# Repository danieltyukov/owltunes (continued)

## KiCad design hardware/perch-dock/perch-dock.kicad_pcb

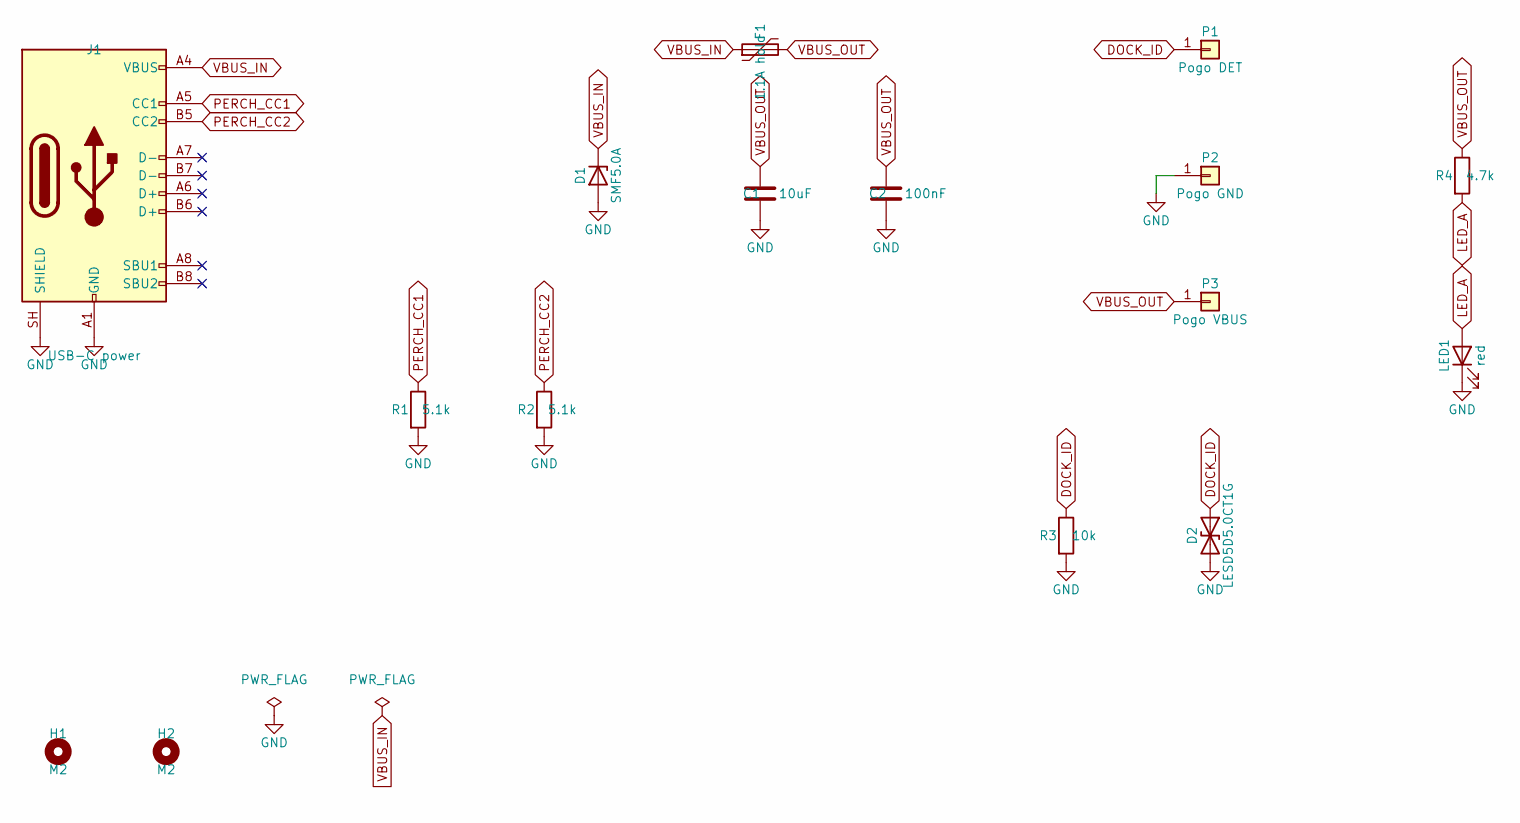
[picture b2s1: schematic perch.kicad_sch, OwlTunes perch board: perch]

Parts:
C1: 10uF; C_0603_1608Metric; MPN CL10A106KP8NNNC; LCSC Part # C19702
C2: 100nF; C_0402_1005Metric; MPN CL05B104KO5NNNC; LCSC Part # C1525
D1: SMF5.0A; D_SOD-123F; MPN SMF5.0A; LCSC Part # C193402
D2: LESD5D5.0CT1G; D_SOD-523; MPN LESD5D5.0CT1G; LCSC Part # C5274290
F1: 1.1A hold; Fuse_1206_3216Metric; MPN nSMD110; LCSC Part # C71465
H1, H2: M2; MountingHole_2.2mm_M2
J1: USB-C power; USB_C_Receptacle_HRO_TYPE-C-31-M-12; MPN TYPE-C-31-M-12; LCSC Part # C165948
LED1: red; LED_0603_1608Metric; MPN KT-0603R; LCSC Part # C2286
P1: Pogo DET; PogoPin_Xinyangze_YZ71215080P-02; MPN YZ71215080P-02; LCSC Part # C5157364
P2: Pogo GND; PogoPin_Xinyangze_YZ71215080P-02; MPN YZ71215080P-02; LCSC Part # C5157364
P3: Pogo VBUS; PogoPin_Xinyangze_YZ71215080P-02; MPN YZ71215080P-02; LCSC Part # C5157364
R1, R2: 5.1k; R_0402_1005Metric; MPN 0402WGF5101TCE; LCSC Part # C25905
R3: 10k; R_0402_1005Metric; MPN 0402WGF1002TCE; LCSC Part # C25744
R4: 4.7k; R_0402_1005Metric; MPN 0402WGF4701TCE; LCSC Part # C25900

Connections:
DOCK_ID: D2.1 (A1), P1.1, R3.1
GND: C1.2, C2.2, D1.2 (A), D2.2 (A2), J1.A1 (GND), J1.A12 (GND), J1.B1 (GND), J1.B12 (GND), J1.SH (SHIELD), LED1.1 (K), P2.1, R1.2, R2.2, R3.2
LED_A: LED1.2 (A), R4.2
PERCH_CC1: J1.A5 (CC1), R1.1
PERCH_CC2: J1.B5 (CC2), R2.1
VBUS_IN: D1.1 (K), F1.1, J1.A4 (VBUS), J1.A9 (VBUS), J1.B4 (VBUS), J1.B9 (VBUS)
VBUS_OUT: C1.1, C2.1, F1.2, P3.1, R4.1

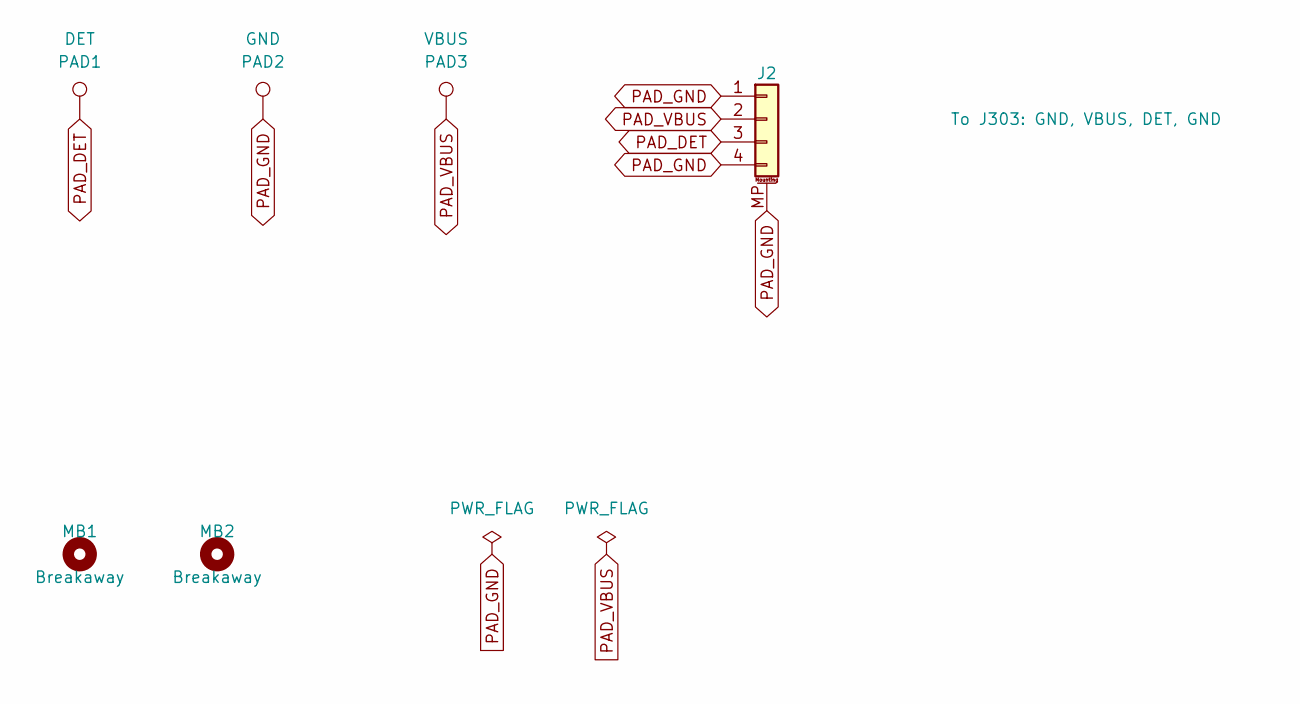
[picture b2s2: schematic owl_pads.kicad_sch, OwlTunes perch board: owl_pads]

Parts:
J2: To J303: GND, VBUS, DET, GND; JST_SH_SM04B-SRSS-TB_1x04-1MP_P1.00mm_Horizontal; MPN SM04B-SRSS-TB(LF)(SN); LCSC Part # C160404
MB1, MB2: Breakaway; MouseBite_2.5mm_2x0.6mm
PAD1: DET; TestPoint_Pad_D3.0mm
PAD2: GND; TestPoint_Pad_D3.0mm
PAD3: VBUS; TestPoint_Pad_D3.0mm

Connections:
PAD_DET: J2.3, PAD1.1
PAD_GND: J2.1, J2.4, J2.MP (MountPin), PAD2.1
PAD_VBUS: J2.2, PAD3.1

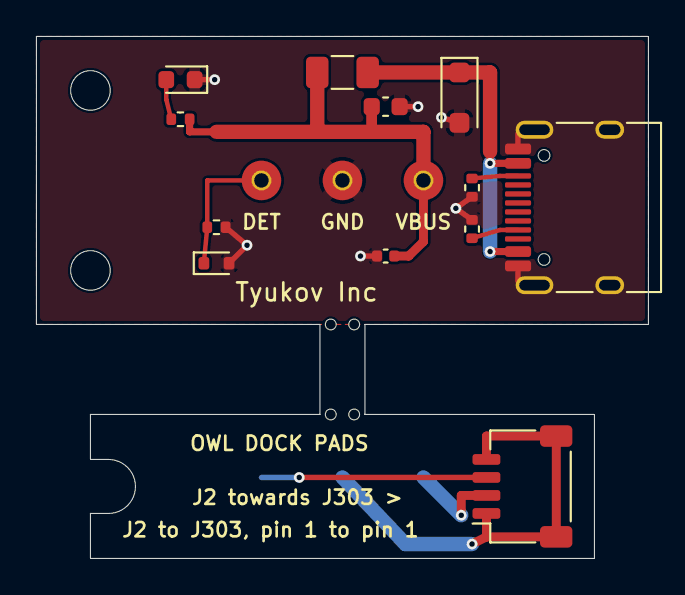
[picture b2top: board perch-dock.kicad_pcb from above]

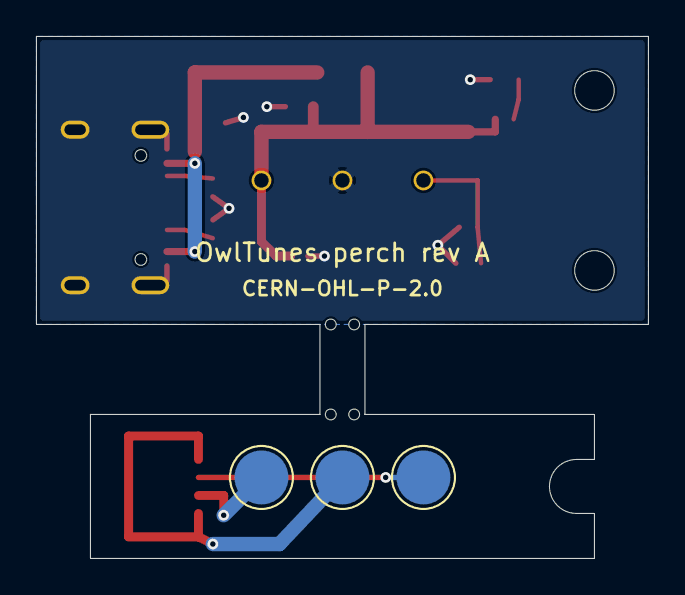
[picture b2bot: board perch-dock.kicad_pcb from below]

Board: 2 copper layers, 34.0 x 29.0 mm, 22 parts (3 on the bottom side), 10 nets.

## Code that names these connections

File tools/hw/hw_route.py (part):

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        ("GND", "via", [(13.85, -3.45), (13.85, -2.55), (12.3, -3.05), (12.3, -3.65), (16.3, -6.7), (16.35, -4.75),
                        (17.2, -0.2), (17.2, 1.4), (13.28, -0.7), (9.8, -1.2)]),
    ],
    # Charger (BQ24073): VIN_CHG from pin 13 to C101, on to the D101 and D102 cathodes; VSYS from
    # pins 10 and 11 to C102 and TP102 (on to the TPS63802 in part C, with a layer change at each
    # end: In2 stays GND under U101, U103 and their caps, so a VSYS pour only runs between them);
    # VBAT from pins 2 and 3 to C103, then up between C103 and R103, clear of the H1 boss ring, to
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    # VIN_CHG taps from the D101/D102 cathode run: east to TP101 above the diode anodes (D101's
    # VBUS_USB anode stays open to the east and south of TP101); and to R103, the CHG_EN2 pull-up,
    # which sits between the VBAT and VSYS runs north of U101, so that tap crosses on F.Cu west of
    # U101 and leaves the ground below U101 pin 1 free for BAT_NTC. Its top via sits at y 1.8, low
    # enough for the +3V3 link (late_links) to pass between it and the VSYS F.Cu run at y 3.25.
    "vin_chg_taps": [
        ("VIN_CHG", 0.5, [(24.1, -4.0), (24.3, -4.2), (29.3, -4.2), (29.3, -5.5)]),
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        ("VIN_CHG", 0.25, [(22.5, 1.8), (22.5, 2.99)]),
        ("VIN_CHG", "via", [(23.4, -4.1), (22.5, 1.8)]),
    ],
    # TPS_PG from U103 pin 5 to R212 on the ESP32 EN network: a via in the pocket west of pin 5
    # (inside the +3V3 and FB runs), F.Cu north, east of the crystal and its load caps (nothing on
    # F.Cu under them), and a via beside R212.
    "tps_pg": [
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        ("XTAL32_P", 0.15, [(8.75, 26.72), (9.9, 26.72), (10.5, 27.35), (12.0, 27.35), (13.92, 27.35)]),
        ("XTAL32_N", 0.15, [(8.75, 25.45), (9.9, 25.45), (10.5, 24.85), (12.0, 24.85), (13.92, 24.85)]),
    ],
    # Dock: VBUS_DOCK from J303 pin 2 through the D301 TVS up the right side, clear of the H4 boss
    # ring and U301, to the D102 anode at 0.5 mm; DOCK_PAD from J303 pin 3 through D302 to R307.
    "dock": [
        ("VBUS_DOCK", 0.5, [(14.5, -28.825), (14.5, -28.0), (16.4, -26.1), (16.4, -24.5), (19.6, -21.3),
                            (19.6, -13.0), (23.5, -10.0), (26.9, -10.0), (26.9, -7.9)]),
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        ("GND", "via", [(1.27, 10.3), (-11.0, 24.18)]),
        ("", "keepout", j301_comb(), "F"),
    ],
    # BAT_NTC from U101 pin 1 (TS) to RT101, the board NTC under the middle of the cell (the pack
    # is 2-wire). B.Cu down at x 22.75 and west at y -2.0 between C103 and R101 (CHG_ISET can pass
    # below at y -2.5) to a via south-west of C103, then F.Cu over In1 GND and across the B.Cu USB
    # pair: diagonally between the C105/C106 GND vias and the H4 hole (under the H4 bezel lug,
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    # the link is F.Cu over the In1 GND plane: two vias beside C105's VSYS pad (the bulk input
    # cap), north at x 13.075 between U103's west and channel GND vias (0.275 mm from each), east
    # at y -1.625 between the channel via and C109's, north at x 16.0 west of the C107/C108 GND
    # vias (not under L101 or the switch pins), east at y 3.25 above the VIN_CHG tap's via, and
    # two vias on the charger's VSYS run below TP102. 0.5 mm all the way.
    "vsys_link": [
        ("VSYS", 0.5, [(13.825, -6.7), (12.85, -6.7), (12.85, -7.55)]),
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    # (Freerouting included, held off by the qspi group's keep-out) runs between the rows or pads.
    # West row: GND pins 1 and 7 join the top mounting pad, pin 31 the bottom one, each mounting
    # pad and pin 25 a via. East row: GND pins 4 and 10 run north past the unused pins to a via
    # above pin 2, pin 20 to a via in the actuator strip (vias only, no parts there). LCD_RST
    # leaves pin 18 east to a via, runs west under J301 on B.Cu and up between the D1 lane and the
    # DISP_3V3 run to a via below TP105, then on F.Cu north at x -8.9 (east of TE) to a via west
    # of module pin 32.
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        ("LCD_RST", 0.1, [(-10.0, 25.45), (-8.75, 25.45)]),
        ("LCD_RST", "via", [(-1.2, 3.85), (-9.2, 8.6), (-10.0, 25.45)]),
    ],
    # DISP_3V3, the panel supply from U104 (TPS22917): J301's west row pins 21 and 23 cannot reach
    # its east row pins 22, 24 and 26 between the rows, so each side has its own via onto one
    # B.Cu run: W west of pins 21 and 23, P in the pocket east of pins 22 to 26 with C302 and C301.
    # The run comes from U104's outputs (pins 5 and 6), C111, C112 and TP105, down at x -10.0 (west
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    ],
    # Touch lines, J301 pins 27 to 30 at 3.3 V (VIEWE's reply of 16 October 2026), to the pull-ups
    # R301 to R303 east of J301 and on to the module:
    # - TP_SDA and TP_INT straight in from J301's east row (pins 28 and 30); TP_SCL (pin 27, west
    #   row) through a via west of J301 and B.Cu under it to a via at (-2.15, -0.95), the one layer
    #   change the order SDA, SCL, INT, RST needs; TP_RST (pin 29) round J301's south end on F.Cu.
    #   All four run east on F.Cu at y -0.3, -0.95, -1.6 and -2.25 to R301 to R303 and the vias
    #   beside them.
    # - DISP_3V3 on from the disp_3v3 run's pocket via P: B.Cu east to x 4.75, north to E (west of
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    #   x 6.6), run north under R301 to R303 and come back up north of R301. All four run west
    #   under the DISP_3V3 crossing (y 2.0 to 3.8), north at x 2.4 to 4.2, west above the QSPI
    #   vias (y 11.55 to 13.05); SDA, SCL and INT drop to B.Cu below module pins 24, 25 and 23,
    #   TP_RST goes on north on F.Cu (it crosses DISP_EN's B.Cu run) to a via east of module pin 33.
    "touch": [
        ("TP_SDA", 0.1, [(-3.4, 0.62), (-2.45, 0.62), (-1.9, 0.07), (-1.9, -0.3), (6.35, -0.3), (7.0, 0.35),
                         (7.39, 0.65)], "F"),
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    # - +3V3, U301 group (U301, C304, C305, R105, R106, R308): F.Cu from that group's via at
    #   (26.28, 2.22) west at y 2.5, between the VIN_CHG tap's via and the VSYS F.Cu run, to a via
    #   beside TP104 on the TPS63802 output.
    # - I2C_SDA, U304 pin 6 (boxed in by the antenna rule area above y 33, U304's own pins and
    #   the +3V3 F.Cu runs): F.Cu west at y 32.8 above ESP_EN's run, north-west beside its
    #   diagonal and west at y 35.2 over the +3V3 vias at x 7.3, a via inside the module's pin
    #   ring and B.Cu under the module to the SDA run from pin 35. The Freerouting GND diagonals
    #   under the module that crossed this path are gone; the B.Cu pour joins those pads.
    # - I2C_SDA, U102 pin 8: a via below the pin, F.Cu north round CHG_PGOOD's via at
    #   (21.65, 13.3) and south at x 20.5, a B.Cu hop under the VSYS and +3V3 F.Cu runs (between
    #   the +3V3 via beside TP104 and TP103), F.Cu south at x 20.55 to the bus via at
    #   (19.929, -11.292) on the U301 side.
    # - IMU_INT1: from U303 pin 12 east at y -6.33 (above I2C_SCL), up a 0.15 mm B.Cu lane at
    #   x 5.3 between DISP_3V3's run to E and the USB pair, under the touch lines and past the
    #   QSPI lanes, a via below module pin 16 and F.Cu on to its run from module pin 6.
    "late_links": [
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
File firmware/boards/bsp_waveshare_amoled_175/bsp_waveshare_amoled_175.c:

/* Waveshare ESP32-S3-Touch-AMOLED-1.75 (ESP32-S3R8, 16 MB flash, 8 MB octal PSRAM): a 466 x 466
 * round AMOLED with a CO5300 over QSPI and a CST9217 touch controller, the owl's development kit.
 *
 * Sources, all fetched on 18 October 2026:
 *   https://github.com/waveshareteam/ESP32-S3-Touch-AMOLED-1.75 (commit e4344e7): HARDWARE_REFERENCE.md
 *     for the pins and I2C addresses, and Waveshare's ESP-IDF BSP (waveshare/esp32_s3_touch_amoled_1_75
 *     3.0.1, in firmware/brookesia/components/) for the init table, the 6-column gap, the touch
 *     mirrors and the 2-pixel rounder.
 *   https://github.com/waveshareteam/Waveshare-ESP32-components (commit 23a6012):
 *     display/touch/esp_lcd_touch_cst9217 for the touch reset and the point read.
 *   https://github.com/espressif/esp-iot-solution (commit 4962410): components/display/lcd/esp_lcd_co5300,
 *     the panel driver Waveshare's BSP uses, for the panel reset timing.
 *
 * Power: Waveshare's BSP and its demos bring up the display and touch without any AXP2101 or TCA9554
 * transaction (the panel runs on the AXP2101's power-on rails), so this does neither, except for one
 * write: the AXP2101's charge current comes from a factory efuse that Waveshare does not document,
 * so it is set to 200 mA, 0.5 C of owl v0's 400 mAh cell (docs/hardware/kit-owl.md). The PWR button,
 * audio, IMU, RTC and SD card are not driven. The kit has no status LED.
 *
 * Not yet run on the kit. The touch mirrors (both on) are the BSP's defaults and live in this
 * board's sdkconfig.board, so they can be changed like rev A's. */
#include "bsp.h"

#include <stdint.h>

#include "driver/gpio.h"
#include "driver/i2c_master.h"
#include "driver/i2c_types.h"
#include "esp_err.h"
#include "esp_log.h"
#include "esp_timer.h"
#include "freertos/FreeRTOS.h"
#include "freertos/task.h"
#include "owl_amoled.h"
#include "owl_ui.h"

_Static_assert(OWL_UI_RES == OWL_CO5300_RES, "the UI is laid out for the 466 x 466 panel");

/* HARDWARE_REFERENCE.md, "ESP32-S3 GPIO assignment" and "Shared I2C bus". */
#define PIN_LCD_CS 12
#define PIN_LCD_CLK 38
#define PIN_LCD_D0 4
#define PIN_LCD_D1 5
#define PIN_LCD_D2 6
#define PIN_LCD_D3 7
#define PIN_LCD_RST 39
#define PIN_TP_RST 40
#define PIN_TP_INT 11
#define PIN_I2C_SCL 14
#define PIN_I2C_SDA 15
#define I2C_ADDR_CST9217 0x5A
#define I2C_ADDR_AXP2101 0x34
/* GPIO13 is the panel's TE output; not used yet. */

#define LCD_QSPI_HZ 40000000 /* CO5300_PANEL_IO_QSPI_CONFIG in esp_lcd_co5300 */
#define I2C_HZ 400000        /* the BSP's CONFIG_BSP_I2C_CLK_SPEED_HZ */

/* AXP2101 datasheet V1.0, REG 62H "ICC charger setting": bits 4:0 give 25 mA steps up to 200 mA
 * (01000), then 100 mA steps; bits 7:5 read as 0. */
#define AXP2101_REG_ICC 0x62
#define AXP2101_ICC_200MA 0x08

static const char *TAG = "bsp_waveshare";

static void wait_ms(uint32_t ms)
{
    vTaskDelay(pdMS_TO_TICKS(ms) + 1); /* at least ms: vTaskDelay(n) can return up to a tick early */
}

static void output(int pin, int level)
{
    ESP_ERROR_CHECK(gpio_set_level(pin, level));
    const gpio_config_t config = {
        .pin_bit_mask = 1ULL << pin,
        .mode = GPIO_MODE_OUTPUT,
        .pull_up_en = GPIO_PULLUP_DISABLE,
        .pull_down_en = GPIO_PULLDOWN_DISABLE,
        .intr_type = GPIO_INTR_DISABLE,
    };
    ESP_ERROR_CHECK(gpio_config(&config));
}

/* On the touch controller's bus, which owl_amoled_touch_create has just made on I2C0. A failed write
 * leaves the efuse default in place, so it is logged and the display carries on. */
static void limit_charge_current(void)
{
    i2c_master_bus_handle_t bus = NULL;
    ESP_ERROR_CHECK(i2c_master_get_bus_handle(I2C_NUM_0, &bus));
    const i2c_device_config_t dev_config = {
        .dev_addr_length = I2C_ADDR_BIT_LEN_7,
        .device_address = I2C_ADDR_AXP2101,
        .scl_speed_hz = I2C_HZ,
    };
    i2c_master_dev_handle_t axp = NULL;
    ESP_ERROR_CHECK(i2c_master_bus_add_device(bus, &dev_config, &axp));
    const uint8_t write[2] = {AXP2101_REG_ICC, AXP2101_ICC_200MA};
    esp_err_t err = i2c_master_transmit(axp, write, sizeof(write), 100);
    if (err != ESP_OK) {
        ESP_LOGE(TAG, "AXP2101 charge current not set: %s", esp_err_to_name(err));
    }
    ESP_ERROR_CHECK(i2c_master_bus_rm_device(axp));
}

lv_display_t *bsp_display_init(void)
{
    /* Panel reset as esp_lcd_co5300 does it: low for 10 ms, then 150 ms before the first command. */
    output(PIN_LCD_RST, 0);
    wait_ms(10);
    ESP_ERROR_CHECK(gpio_set_level(PIN_LCD_RST, 1));
    wait_ms(150);

    const owl_amoled_panel_t panel = {
        .pin_cs = PIN_LCD_CS,
        .pin_clk = PIN_LCD_CLK,
        .pin_d0 = PIN_LCD_D0,
        .pin_d1 = PIN_LCD_D1,
        .pin_d2 = PIN_LCD_D2,
        .pin_d3 = PIN_LCD_D3,
        .pclk_hz = LCD_QSPI_HZ,
        .init = owl_co5300_init_waveshare_175,
        .init_len = owl_co5300_init_waveshare_175_len,
        .col_offset = OWL_CO5300_WAVESHARE_175_COL_OFFSET,
    };
    lv_display_t *disp = owl_amoled_display_create(&panel);

    /* Touch reset as esp_lcd_touch_cst9217 does it: low for 10 ms, then 50 ms before the first read. */
    output(PIN_TP_RST, 0);
    wait_ms(10);
    ESP_ERROR_CHECK(gpio_set_level(PIN_TP_RST, 1));
    int64_t released = esp_timer_get_time();

    /* GPIO14 and GPIO15 are the board's shared I2C bus (also the AXP2101 at 0x34, the TCA9554 at
     * 0x20 and the sensors); code that drives those later must reuse this bus on I2C0. */
    const owl_amoled_touch_t touch = {
        .chip = OWL_TOUCH_CST9217,
        .i2c_port = I2C_NUM_0,
        .pin_sda = PIN_I2C_SDA,
        .pin_scl = PIN_I2C_SCL,
        .pin_int = PIN_TP_INT,
        .int_pullup = true, /* as Waveshare's CST9217 example (INPUT_PULLUP) */
        .addr = I2C_ADDR_CST9217,
        .scl_hz = I2C_HZ,
        .ready_at_us = released + 50 * 1000LL,
    };
    owl_amoled_touch_create(disp, &touch);
    limit_charge_current();
    return disp;
}

void bsp_status_led(uint8_t r, uint8_t g, uint8_t b)
{
    /* The kit has no status LED. */
    (void)r;
    (void)g;
    (void)b;
}

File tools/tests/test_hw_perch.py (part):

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MAIN = ROOT / "hardware" / "owl-mainboard"
PIN_X = {"P1": -P.DOCK_PAD_PITCH, "P2": 0.0, "P3": P.DOCK_PAD_PITCH}
PAD_X = {"PAD1": -P.DOCK_PAD_PITCH, "PAD2": 0.0, "PAD3": P.DOCK_PAD_PITCH}
PIN_NET = {"PAD_DET": "DOCK_ID", "PAD_GND": "GND", "PAD_VBUS": "VBUS_OUT"}
LINK = {"PAD_GND": "GND", "PAD_VBUS": "VBUS_DOCK", "PAD_DET": "DOCK_PAD"}


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
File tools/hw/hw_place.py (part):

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    "C111": (-11.6, 12.4, 0, "back"),
    "C112": (-14.2, 12.4, 0, "back"),
    "TP105": (-8.6, 9.6, 0, "back"),
    # Display FPC decoupling on the front, east of J301's DISP_3V3 pins 22, 24 and 26 (J301 sits at
    # (-5.0, 4.22) rot 270 with its rows along y and the flex entering from the west), pad 1
    # towards J301 and outside the strip x -3.7 to -2.4 where J301's back-flip actuator opens.
    "C301": (-1.2, 3.0, 0, "front"),
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    "R301": (7.9, 0.65, 180, "front"),
    "R302": (7.9, -0.95, 180, "front"),
    "R303": (7.9, -2.55, 180, "front"),
    # Haptics next to J302: LRA_P and LRA_N (pins 7 and 9) face the connector; C304 spans VDD
    # pin 10 and GND pin 8 on the outer side, C303 at REG.
    "U301": (25.0, -14.0, 0, "back"),
    "C303": (22.6, -16.4, 0, "back"),
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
